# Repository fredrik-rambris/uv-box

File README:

A UV exposure box with timer based on LEDs by Fredrik Rambris

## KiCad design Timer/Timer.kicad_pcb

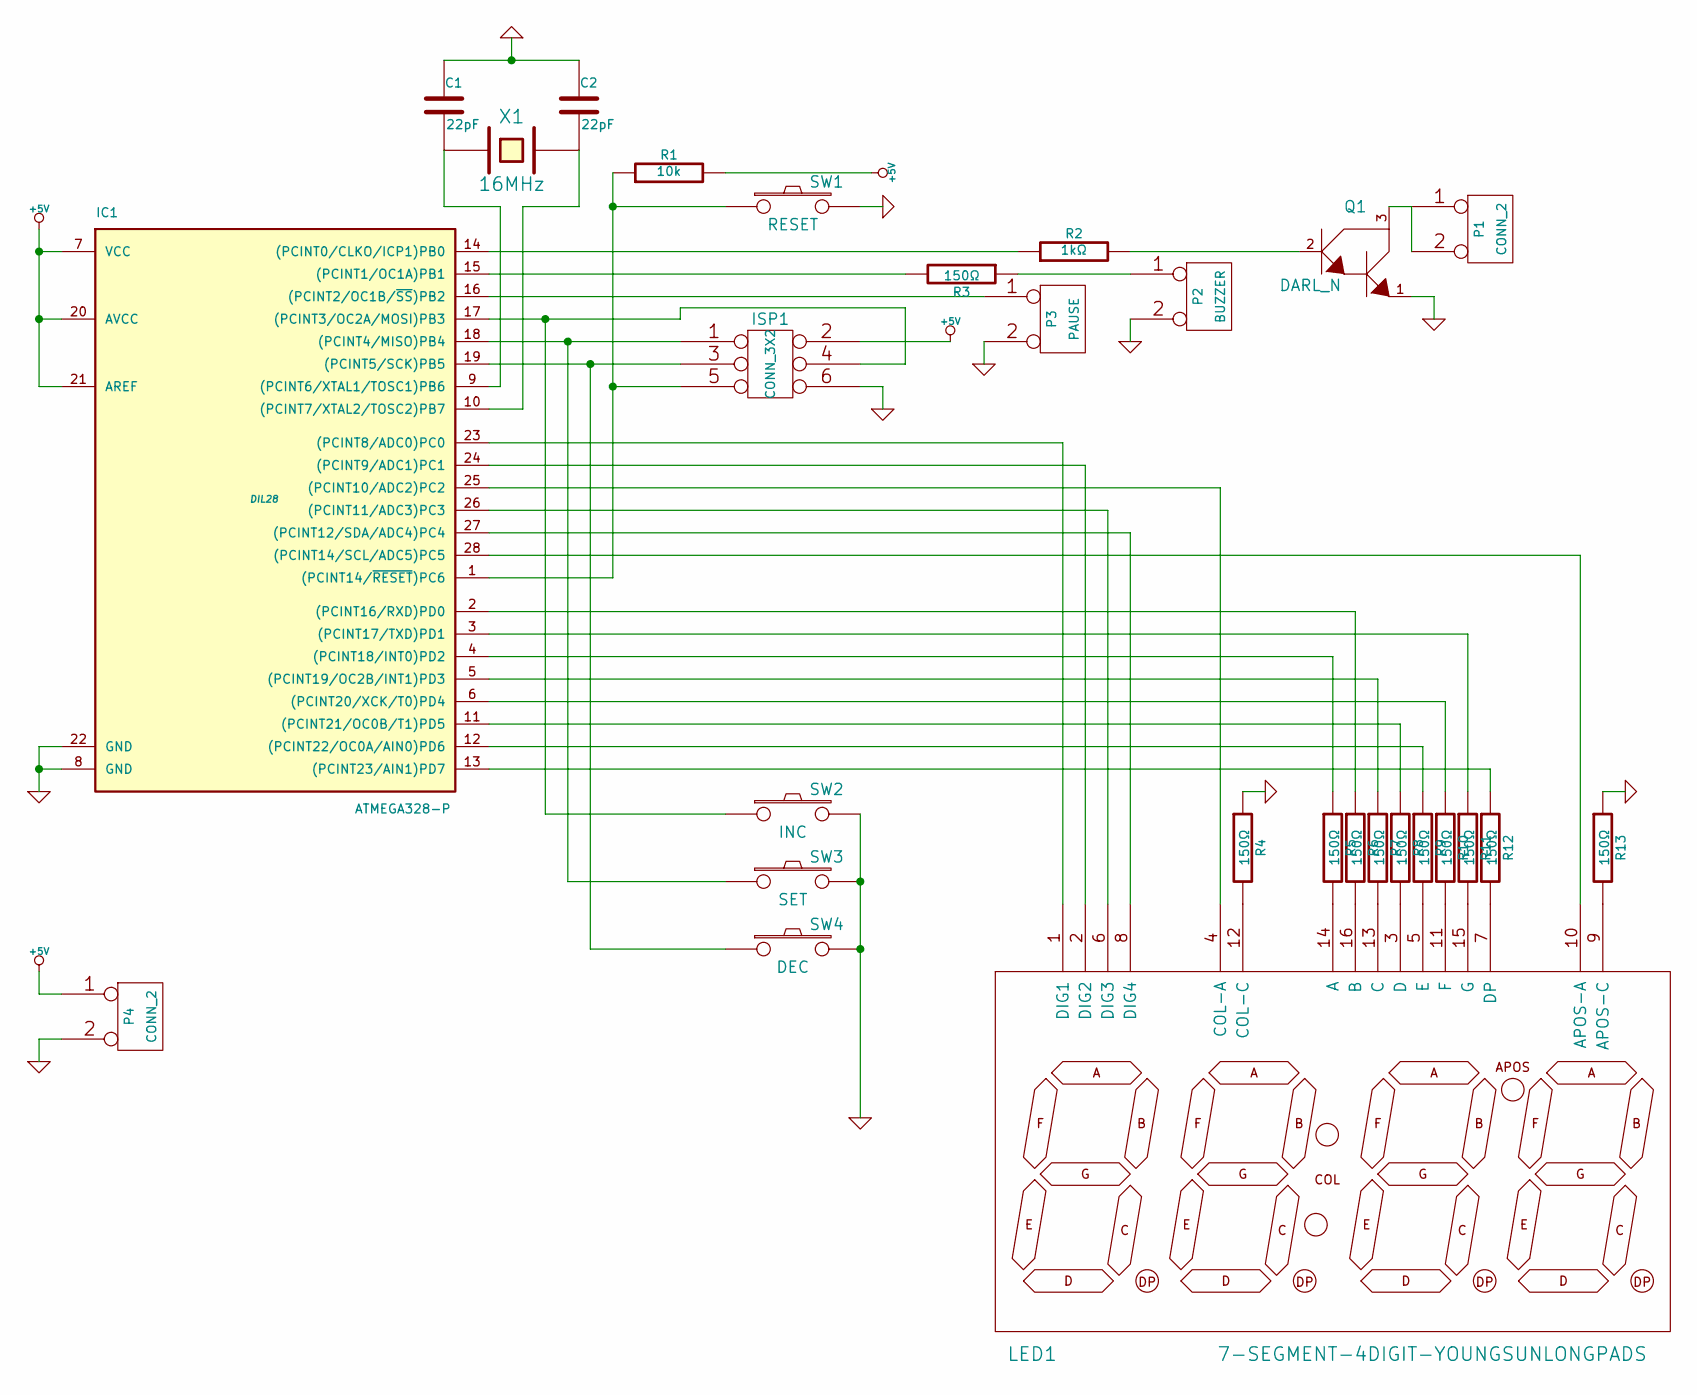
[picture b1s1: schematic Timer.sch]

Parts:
C1, C2: 22pF
IC1: ATMEGA328-P; DIL28
ISP1: CONN_3X2
LED1: 7-SEGMENT-4DIGIT-YOUNGSUNLONGPADS
P1, P4: CONN_2
P2: BUZZER
P3: PAUSE
Q1: DARL_N
R1: 10k
R2: 1kΩ
R3, R4, R5, R6, R7, R8, R9, R10, R11, R12, R13: 150Ω
SW1: RESET
SW2: INC
SW3: SET
SW4: DEC
X1: 16MHz

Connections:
+5V: IC1.7 (VCC), IC1.20 (AVCC), IC1.21 (AREF), ISP1.2, P4.1, R1.2
GND: C1.1, C2.1, IC1.8 (GND), IC1.22 (GND), ISP1.6, P2.2 (PM), P3.2 (PM), P4.2 (PM), Q1.1, R4.1, R13.1, SW1.2, SW2.2, SW3.2, SW4.2
unnamed: C1.2, IC1.9 ((PCINT6/XTAL1/TOSC1)PB6), X1.1
unnamed: C2.2, IC1.10 ((PCINT7/XTAL2/TOSC2)PB7), X1.2
unnamed: IC1.28 ((PCINT14/SCL/ADC5)PC5), LED1.10 (APOS-A)
unnamed: IC1.23 ((PCINT8/ADC0)PC0), LED1.1 (DIG1)
unnamed: IC1.24 ((PCINT9/ADC1)PC1), LED1.2 (DIG2)
unnamed: IC1.25 ((PCINT10/ADC2)PC2), LED1.4 (COL-A)
unnamed: IC1.26 ((PCINT11/ADC3)PC3), LED1.6 (DIG3)
unnamed: IC1.27 ((PCINT12/SDA/ADC4)PC4), LED1.8 (DIG4)
unnamed: IC1.2 ((PCINT16/RXD)PD0), R6.1
unnamed: P1.1, P1.2 (PM), Q1.3
unnamed: IC1.11 ((PCINT21/OC0B/T1)PD5), R8.1
unnamed: IC1.3 ((PCINT17/TXD)PD1), R11.1
unnamed: IC1.4 ((PCINT18/INT0)PD2), R5.1
unnamed: IC1.5 ((PCINT19/OC2B/INT1)PD3), R7.1
unnamed: IC1.6 ((PCINT20/XCK/T0)PD4), R10.1
unnamed: P2.1, R3.1
unnamed: IC1.15 ((PCINT1/OC1A)PB1), R3.2
unnamed: IC1.16 ((PCINT2/OC1B/~SS~)PB2), P3.1
unnamed: IC1.14 ((PCINT0/CLKO/ICP1)PB0), R2.1
unnamed: Q1.2, R2.2
unnamed: LED1.16 (B), R6.2
unnamed: LED1.3 (D), R8.2
unnamed: LED1.5 (E), R9.2
unnamed: LED1.7 (DP), R12.2
unnamed: LED1.9 (APOS-C), R13.2
unnamed: LED1.11 (F), R10.2
unnamed: LED1.12 (COL-C), R4.2
unnamed: LED1.13 (C), R7.2
unnamed: LED1.14 (A), R5.2
unnamed: LED1.15 (G), R11.2
unnamed: IC1.1 ((PCINT14/~RESET~)PC6), ISP1.5, R1.1, SW1.1
unnamed: IC1.12 ((PCINT22/OC0A/AIN0)PD6), R9.1
unnamed: IC1.13 ((PCINT23/AIN1)PD7), R12.1
unnamed: IC1.17 ((PCINT3/OC2A/MOSI)PB3), ISP1.4, SW2.1
unnamed: IC1.18 ((PCINT4/MISO)PB4), ISP1.1, SW3.1
unnamed: IC1.19 ((PCINT5/SCK)PB5), ISP1.3, SW4.1

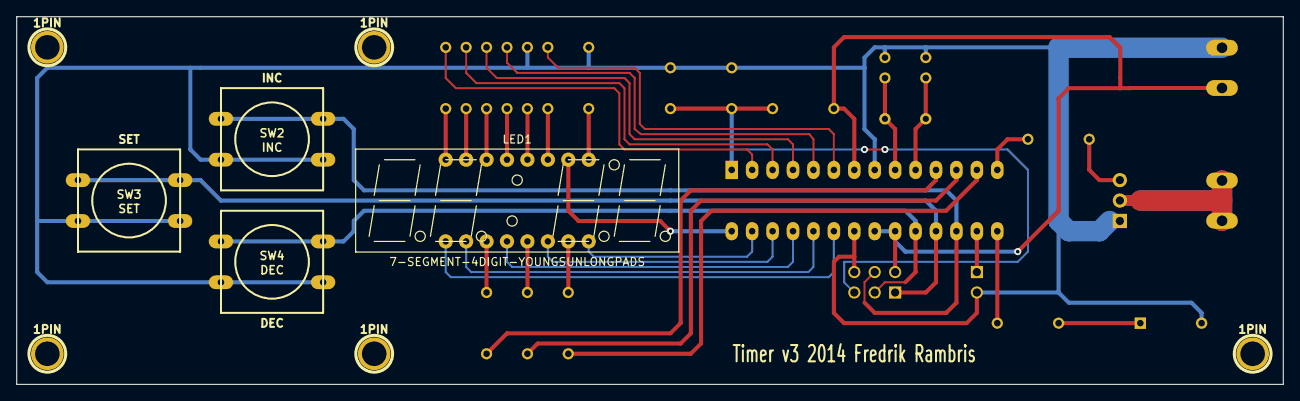
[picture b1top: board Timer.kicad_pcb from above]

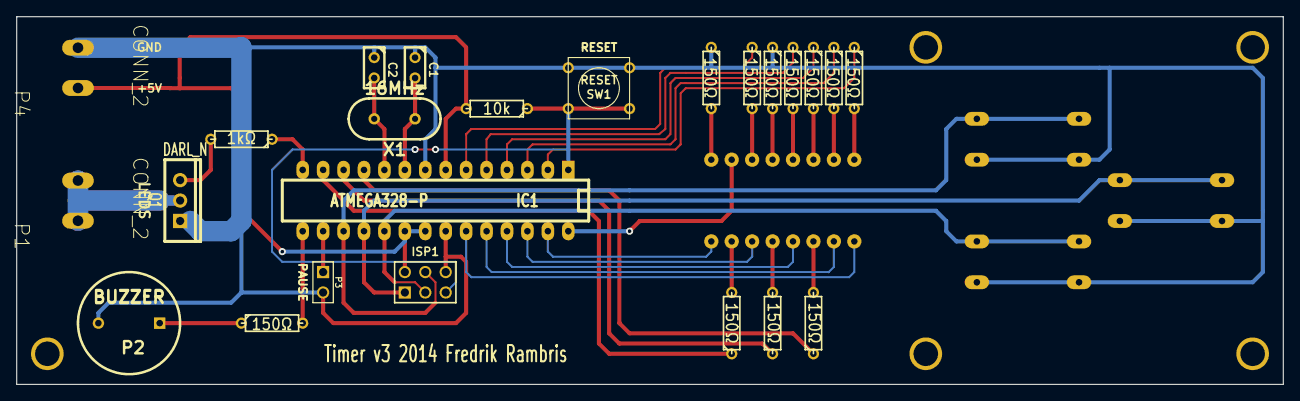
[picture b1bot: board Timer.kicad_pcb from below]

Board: 2 copper layers, 157.5 x 45.7 mm, 33 parts (24 on the bottom side), 38 nets.

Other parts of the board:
1PIN, 1PIN#2, 1PIN#3, 1PIN#4, 1PIN#5: P***; 1pin

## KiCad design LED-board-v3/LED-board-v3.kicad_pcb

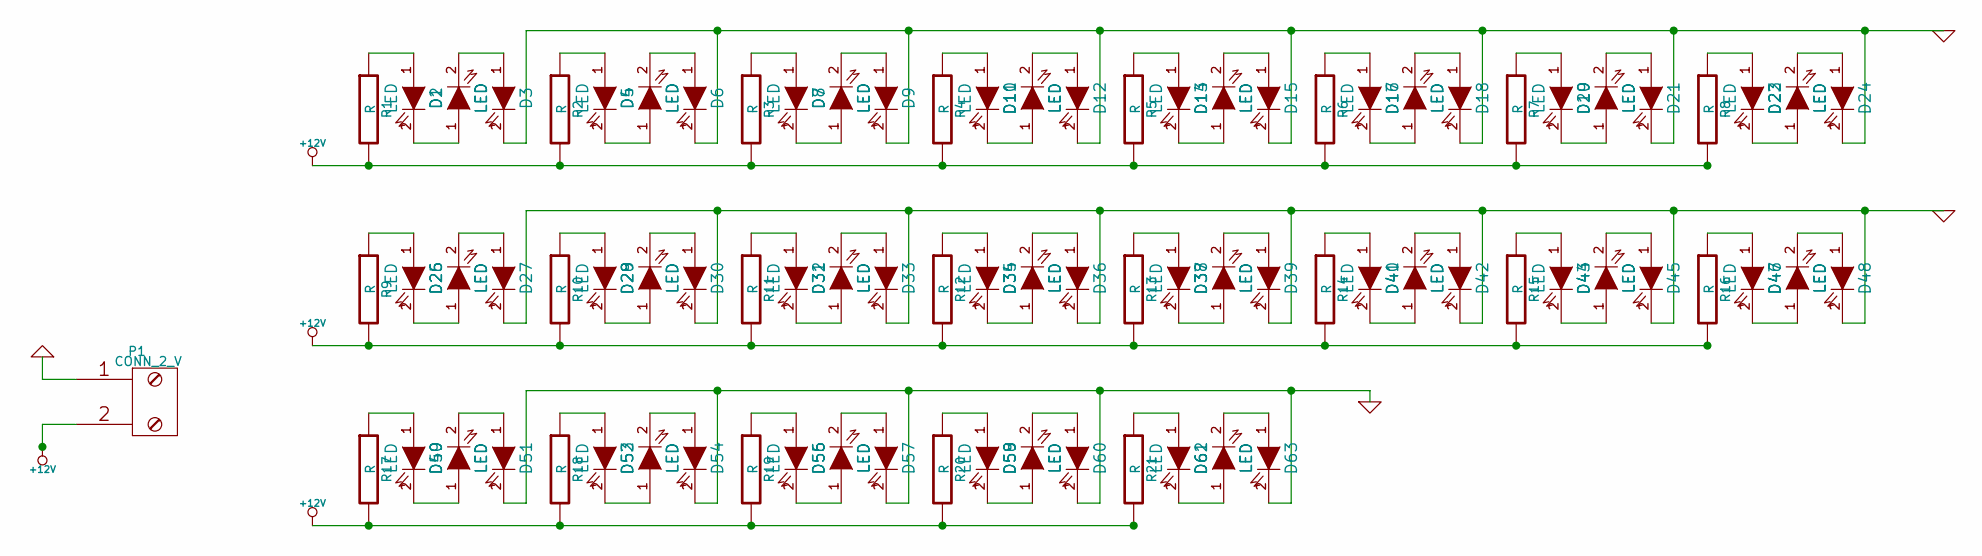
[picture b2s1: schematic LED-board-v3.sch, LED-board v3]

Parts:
D1, D2, D3, D4, D5, D6, D7, D8, D9, D10, D11, D12, D13, D14, D15, D16, D17, D18, D19, D20, D21, D22, D23, D24, D25, D26, D27, D28, D29, D30, D31, D32, D33, D34, D35, D36, D37, D38, D39, D40, D41, D42, D43, D44, D45, D46, D47, D48, D49, D50, D51, D52, D53, D54, D55, D56, D57, D58, D59, D60, D61, D62, D63: LED
P1: CONN_2_V
R1, R2, R3, R4, R5, R6, R7, R8, R9, R10, R11, R12, R13, R14, R15, R16, R17, R18, R19, R20, R21: R

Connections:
+12V: P1.2, R1.2, R2.2, R3.2, R4.2, R5.2, R6.2, R7.2, R8.2, R9.2, R10.2, R11.2, R12.2, R13.2, R14.2, R15.2, R16.2, R17.2, R18.2, R19.2, R20.2, R21.2
GND: D3.2 (K), D6.2 (K), D9.2 (K), D12.2 (K), D15.2 (K), D18.2 (K), D21.2 (K), D24.2 (K), D27.2 (K), D30.2 (K), D33.2 (K), D36.2 (K), D39.2 (K), D42.2 (K), D45.2 (K), D48.2 (K), D51.2 (K), D54.2 (K), D57.2 (K), D60.2 (K), D63.2 (K), P1.1
unnamed: D49.1 (A), R17.1
unnamed: D49.2 (K), D50.1 (A)
unnamed: D46.1 (A), R16.1
unnamed: D47.2 (K), D48.1 (A)
unnamed: D46.2 (K), D47.1 (A)
unnamed: D53.2 (K), D54.1 (A)
unnamed: D52.2 (K), D53.1 (A)
unnamed: D52.1 (A), R18.1
unnamed: D50.2 (K), D51.1 (A)
unnamed: D40.1 (A), R14.1
unnamed: D41.2 (K), D42.1 (A)
unnamed: D40.2 (K), D41.1 (A)
unnamed: D37.1 (A), R13.1
unnamed: D38.2 (K), D39.1 (A)
unnamed: D37.2 (K), D38.1 (A)
unnamed: D43.2 (K), D44.1 (A)
unnamed: D43.1 (A), R15.1
unnamed: D44.2 (K), D45.1 (A)
unnamed: D59.2 (K), D60.1 (A)
unnamed: D58.2 (K), D59.1 (A)
unnamed: D58.1 (A), R20.1
unnamed: D55.1 (A), R19.1
unnamed: D56.2 (K), D57.1 (A)
unnamed: D55.2 (K), D56.1 (A)
unnamed: D61.2 (K), D62.1 (A)
unnamed: D61.1 (A), R21.1
unnamed: D62.2 (K), D63.1 (A)
unnamed: D13.2 (K), D14.1 (A)
unnamed: D13.1 (A), R5.1
unnamed: D14.2 (K), D15.1 (A)
unnamed: D16.1 (A), R6.1
unnamed: D10.1 (A), R4.1
unnamed: D11.2 (K), D12.1 (A)
unnamed: D10.2 (K), D11.1 (A)
unnamed: D20.2 (K), D21.1 (A)
unnamed: D19.2 (K), D20.1 (A)
unnamed: D19.1 (A), R7.1
unnamed: D17.2 (K), D18.1 (A)
unnamed: D16.2 (K), D17.1 (A)
unnamed: D4.2 (K), D5.1 (A)
unnamed: D5.2 (K), D6.1 (A)
unnamed: D4.1 (A), R2.1
unnamed: D1.1 (A), R1.1
unnamed: D2.2 (K), D3.1 (A)
unnamed: D1.2 (K), D2.1 (A)
unnamed: D7.1 (A), R3.1
unnamed: D8.2 (K), D9.1 (A)
unnamed: D7.2 (K), D8.1 (A)
unnamed: D29.2 (K), D30.1 (A)
unnamed: D32.2 (K), D33.1 (A)
unnamed: D31.2 (K), D32.1 (A)
unnamed: D31.1 (A), R11.1
unnamed: D28.1 (A), R10.1
unnamed: D28.2 (K), D29.1 (A)
unnamed: D35.2 (K), D36.1 (A)
unnamed: D34.1 (A), R12.1
unnamed: D34.2 (K), D35.1 (A)
unnamed: D22.1 (A), R8.1
unnamed: D23.2 (K), D24.1 (A)
unnamed: D22.2 (K), D23.1 (A)
unnamed: D25.1 (A), R9.1
unnamed: D26.2 (K), D27.1 (A)
unnamed: D25.2 (K), D26.1 (A)

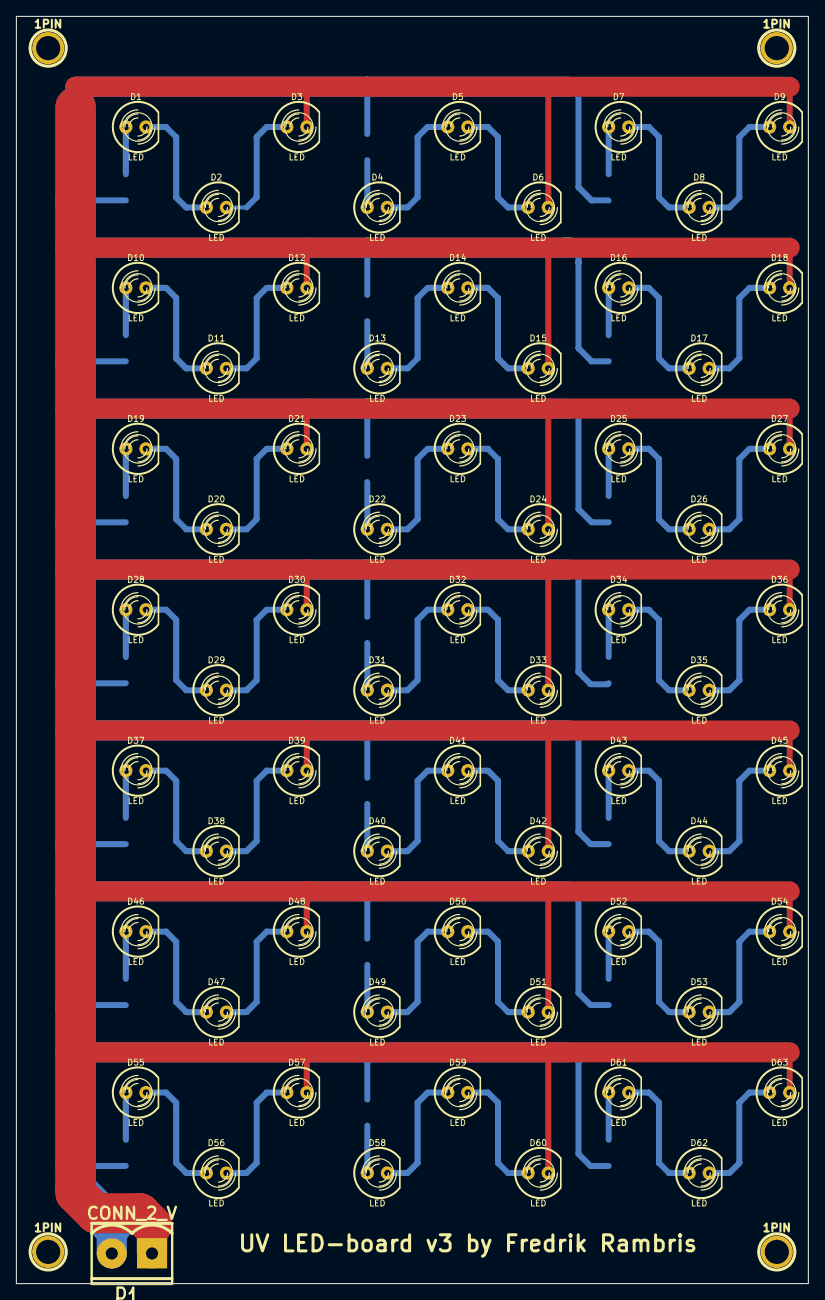
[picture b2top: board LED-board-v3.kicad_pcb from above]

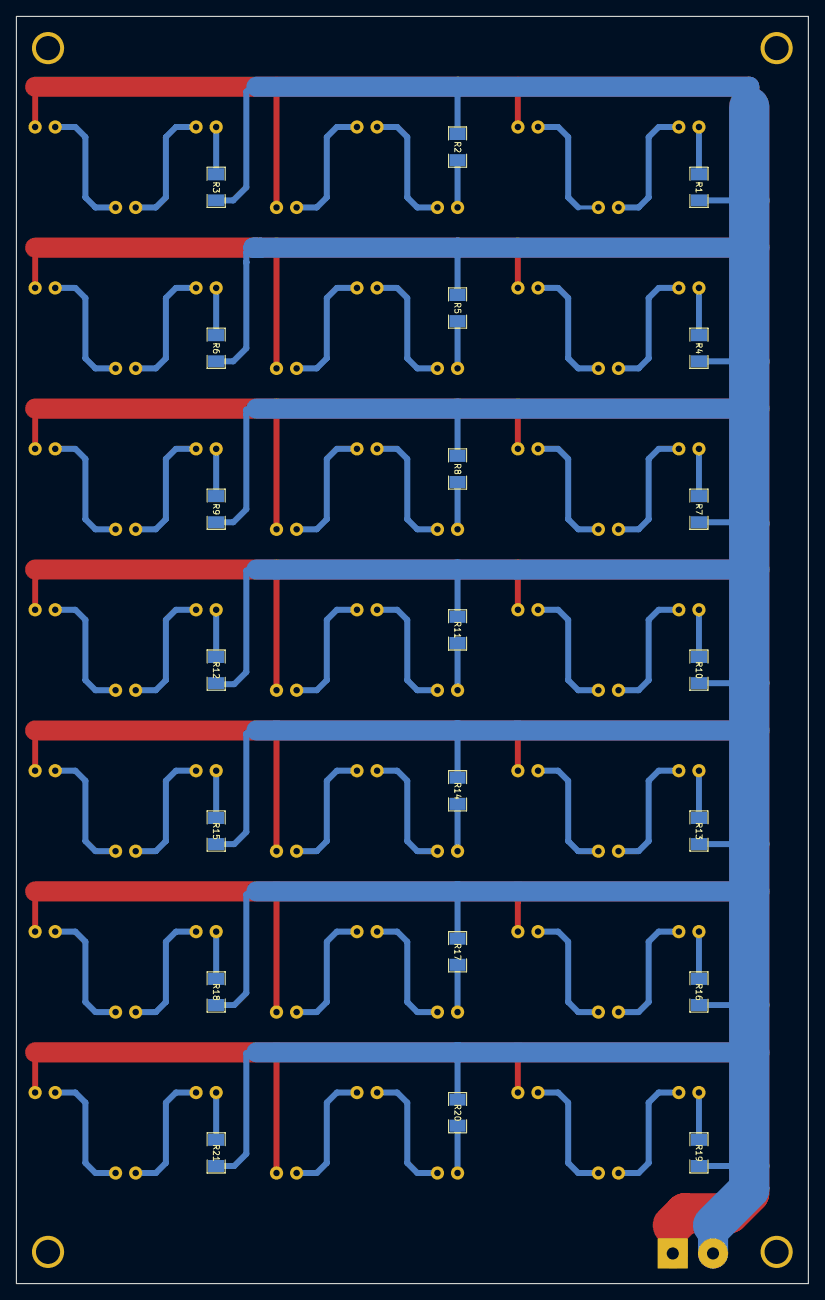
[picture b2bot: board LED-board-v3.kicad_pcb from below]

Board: 2 copper layers, 100.0 x 160.0 mm, 89 parts (21 on the bottom side), 65 nets.

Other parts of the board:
1PIN, 1PIN#2, 1PIN#3, 1PIN#4: P***; 1pin

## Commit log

2014-11-30 Added license
2015-05-30 Added Sketchup model of UV-Box
